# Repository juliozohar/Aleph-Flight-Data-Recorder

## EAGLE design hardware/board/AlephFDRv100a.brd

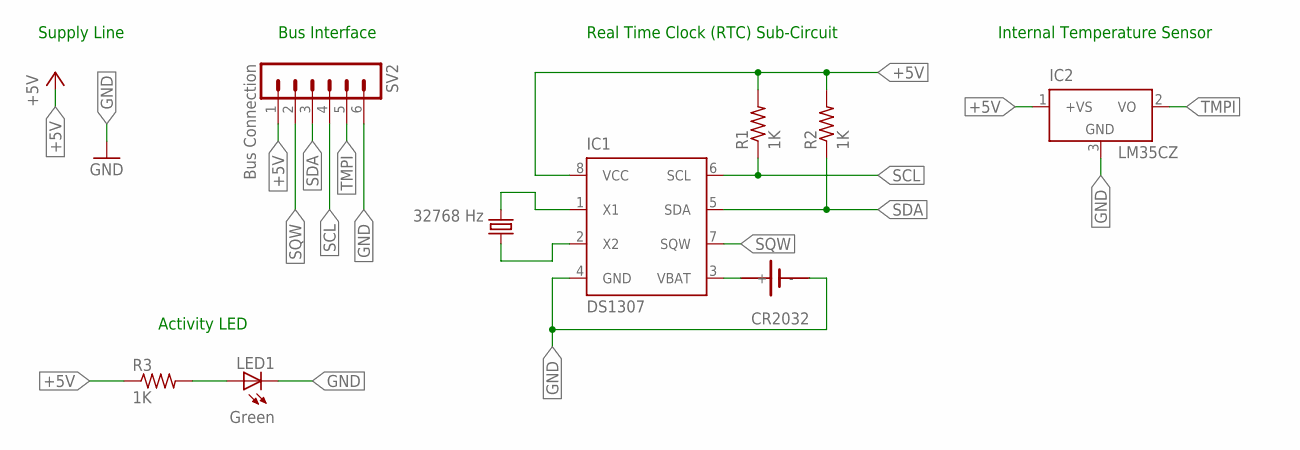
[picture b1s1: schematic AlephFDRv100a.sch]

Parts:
BAT1: CR2032; SN2032
IC1: DS1307; DIL08
IC2: LM35CZ; TO92
LED1: Green; LED3MM
Q1: 32768 Hz; TC26H
R1, R2, R3: 1K; 0207/10
SV2: Bus Connection; MA06-1

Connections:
+5V: IC1.8 (VCC), IC2.1 (+VS), R1.2, R2.2, R3.1, SV2.1
GND: BAT1.-, IC1.4 (GND), IC2.3 (GND), LED1.K (C), SV2.6
unnamed: LED1.A, R3.2
unnamed: IC1.1 (X1), Q1.2
unnamed: IC1.2 (X2), Q1.1
unnamed: BAT1.+, IC1.3 (VBAT)
SCL: IC1.6 (SCL), R1.1, SV2.4
SDA: IC1.5 (SDA), R2.1, SV2.3
SQW: IC1.7 (SQW), SV2.2
TMPI: IC2.2 (VO), SV2.5

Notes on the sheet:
Activity LED
Real Time Clock (RTC) Sub-Circuit
Supply Line
Bus Interface
Internal Temperature Sensor

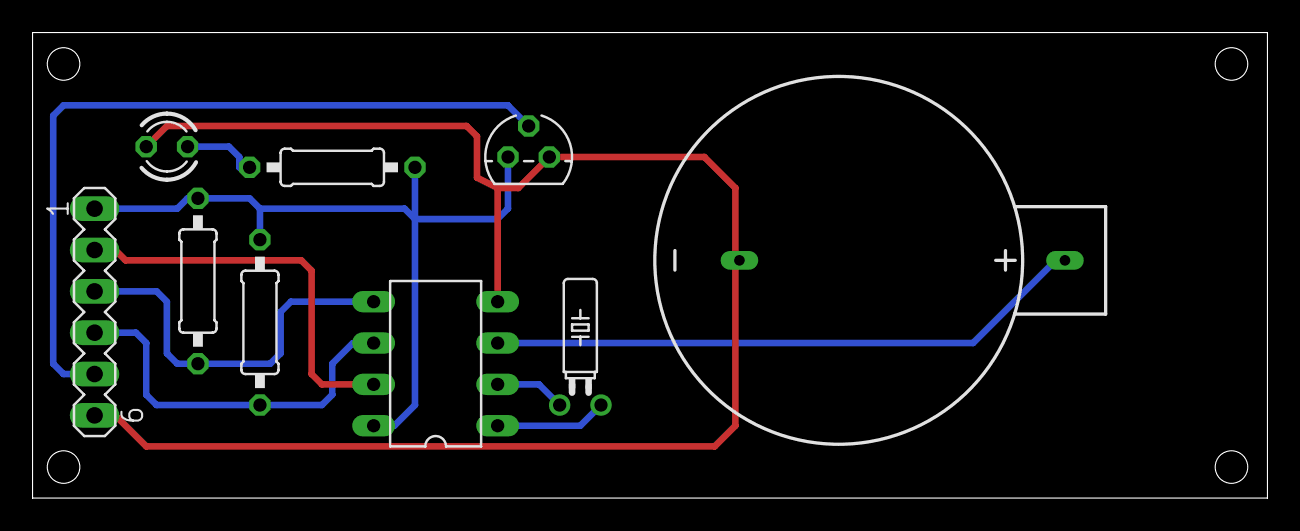
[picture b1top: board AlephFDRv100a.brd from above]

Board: 2 copper layers, 75.9 x 28.6 mm, 9 parts (0 on the bottom side), 10 nets.

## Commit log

2015-03-01 Aleph Flight Data Recorder Project
    Source code for all software implementations for the Aleph Flight Data
    Recorder implementations.
2015-03-06 Firmware commit
2015-03-06 Board commit
2015-03-06 Source documenting
    Update for various source documenting purposes.
2015-03-06 Fix counter variable.
    Fixes tmp_cont variable for out string size.
2015-03-08 Documentation
    Add documentation to repository.
